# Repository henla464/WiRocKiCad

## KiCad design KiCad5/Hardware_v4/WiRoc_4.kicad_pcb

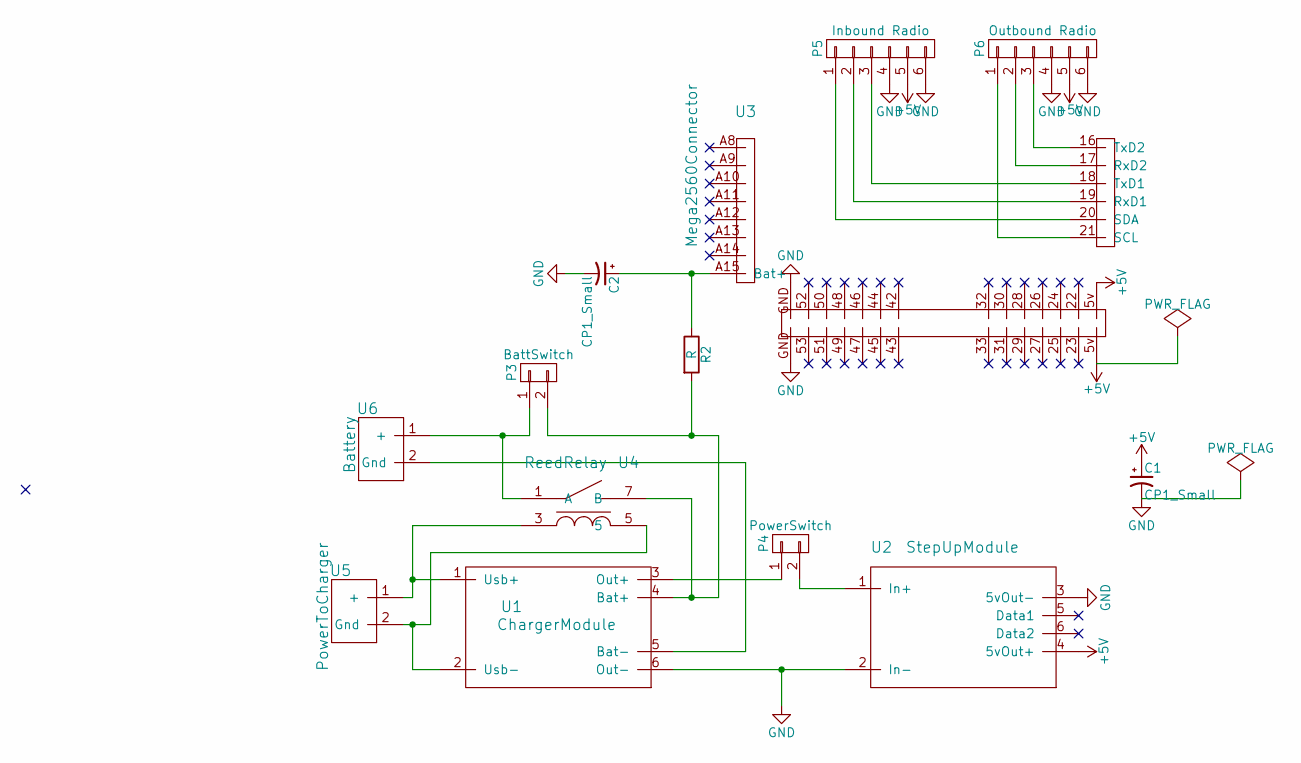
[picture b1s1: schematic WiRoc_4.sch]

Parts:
C1, C2: CP1_Small; C_Radial_D5_L11_P2
P3: BattSwitch; Pin_Header_Straight_1x02
P4: PowerSwitch; Pin_Header_Straight_1x02
P5: Inbound Radio; Pin_Header_Straight_1x06
P6: Outbound Radio; Pin_Header_Straight_1x06
R2: R; Resistor_Horizontal_RM10mm
U1: ChargerModule
U2: StepUpModule
U3: Mega2560Connector
U4: ReedRelay; SIP-1A05
U5: PowerToCharger; JST_2.56
U6: Battery; JST_2.56

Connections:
+5V: C1.1, P5.5, P6.5, U2.4 (5vOut+), U3.5v
GND: C1.2, C2.2, P5.4, P5.6, P6.4, P6.6, U1.6 (Out-), U2.2 (In-), U2.3 (5vOut-), U3.GND
unnamed: C2.1, R2.1, U3.A15 (Bat+)
unnamed: P3.1, U4.1 (A), U6.1 (+)
unnamed: P3.2, R2.2, U1.4 (Bat+), U4.7 (B)
unnamed: P4.1, U1.3 (Out+)
unnamed: P4.2, U2.1 (In+)
unnamed: P5.1, U3.20 (SDA)
unnamed: P5.2, U3.19 (RxD1)
unnamed: P5.3, U3.18 (TxD1)
unnamed: P6.1, U3.21 (SCL)
unnamed: P6.2, U3.17 (RxD2)
unnamed: P6.3, U3.16 (TxD2)
unnamed: U1.1 (Usb+), U4.3, U5.1 (+)
unnamed: U1.2 (Usb-), U4.5, U5.2 (Gnd)
unnamed: U1.5 (Bat-), U6.2 (Gnd)

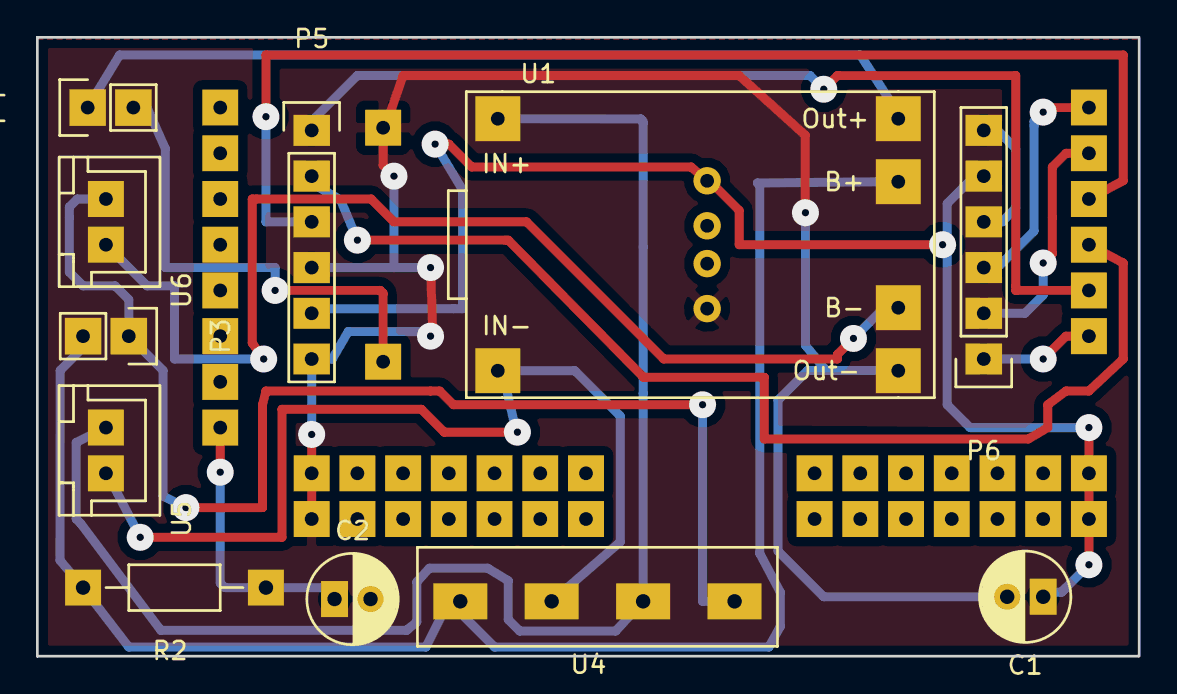
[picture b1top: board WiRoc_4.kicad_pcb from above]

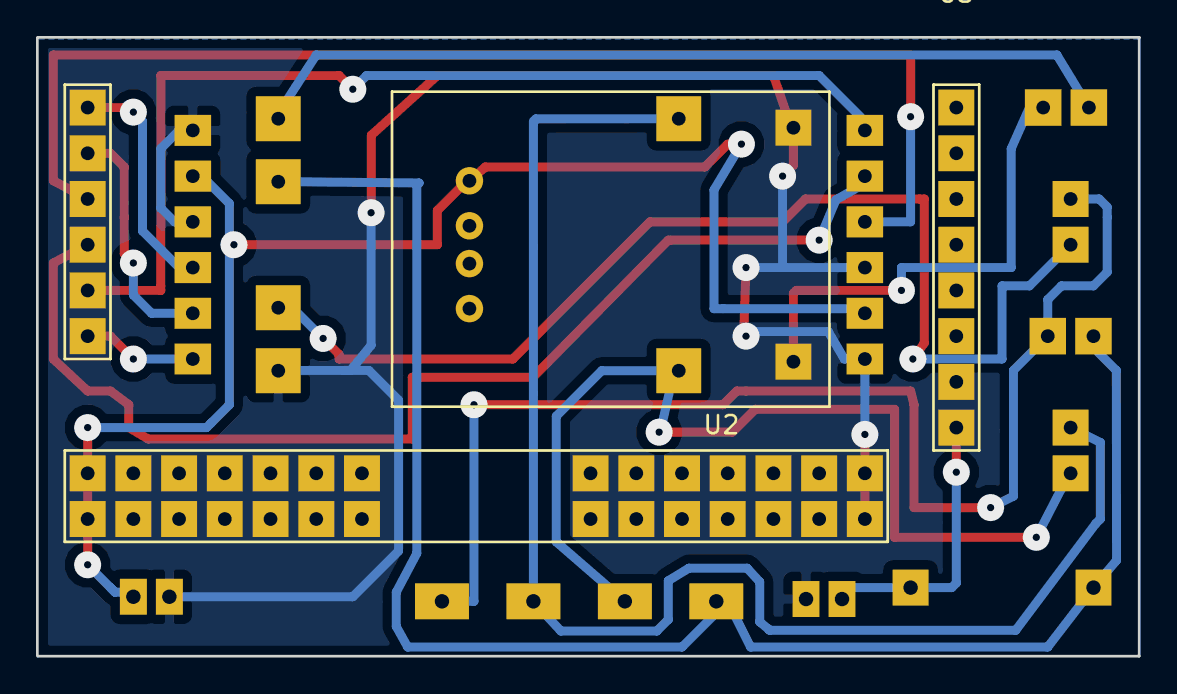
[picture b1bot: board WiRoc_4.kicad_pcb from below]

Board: 2 copper layers, 61.2 x 34.4 mm, 13 parts (2 on the bottom side), 16 nets.

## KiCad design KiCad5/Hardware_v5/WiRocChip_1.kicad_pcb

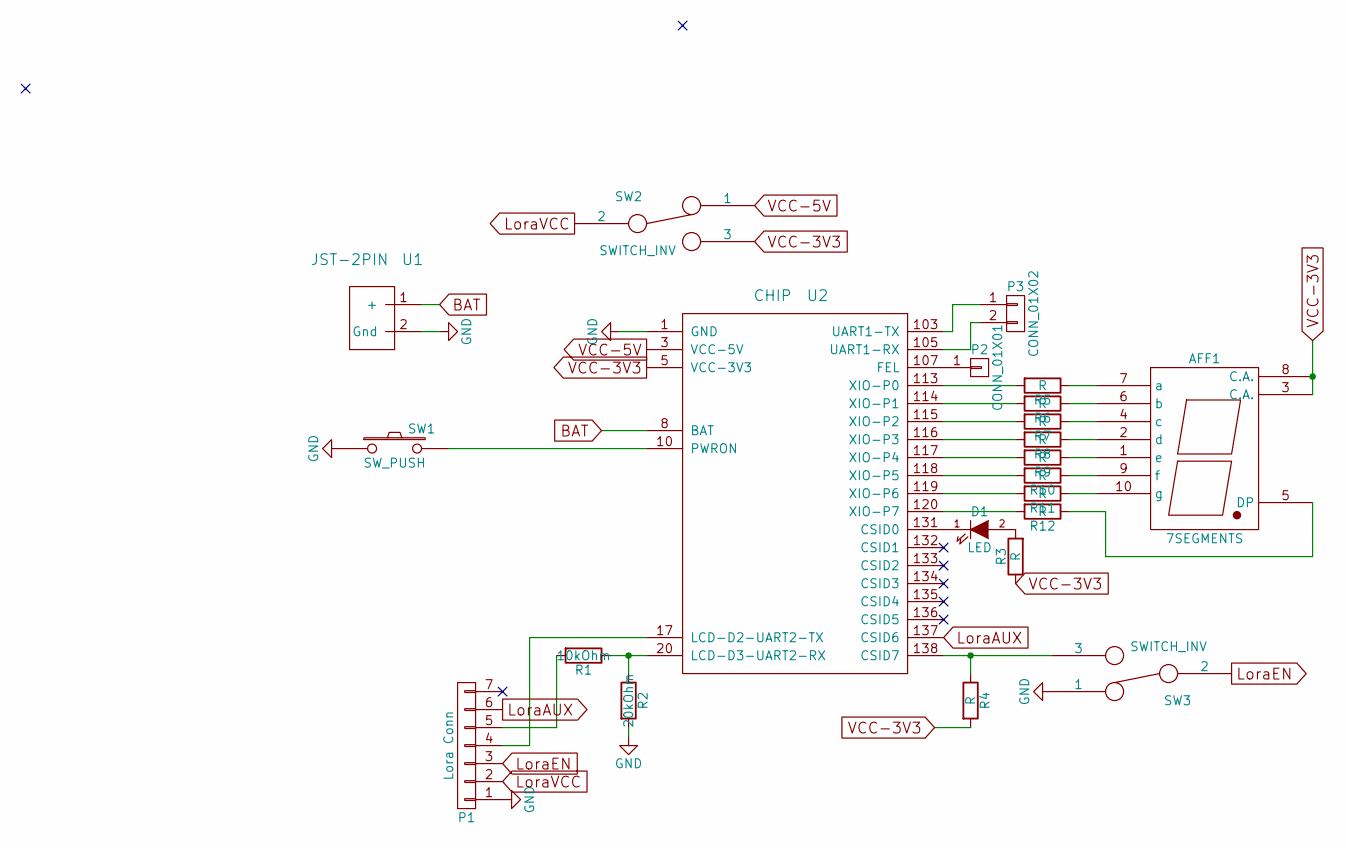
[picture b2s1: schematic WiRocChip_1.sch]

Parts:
AFF1: 7SEGMENTS; 7SegmentLED_LTS6760_LTS6780
D1: LED; LED_D3.0mm
P1: Lora Conn; Pin_Header_Straight_1x07_Pitch2.54mm
P2: CONN_01X01; Pin_Header_Straight_1x01_Pitch2.54mm
P3: CONN_01X02; Pin_Header_Straight_1x02_Pitch2.54mm
R1: 10kOhm; R_Axial_DIN0207_L6.3mm_D2.5mm_P7.62mm_Horizontal
R2: 20kOhm; R_Axial_DIN0207_L6.3mm_D2.5mm_P7.62mm_Horizontal
R3, R4, R5, R6, R7, R8, R9, R10, R11, R12: R; R_Axial_DIN0207_L6.3mm_D2.5mm_P7.62mm_Horizontal
SW1: SW_PUSH; Pin_Header_Straight_1x02_Pitch2.54mm
SW2, SW3: SWITCH_INV; Pin_Header_Straight_1x03_Pitch2.54mm
U1: JST-2PIN; JST_2.56
U2: CHIP; Chip

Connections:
BAT: U1.1 (+), U2.8 (BAT)
GND: P1.1, R2.2, SW1.1, SW3.1, U1.2 (Gnd), U2.1 (GND)
LoraAUX: P1.6, U2.137 (CSID6)
LoraEN: P1.3, SW3.2
LoraVCC: P1.2, SW2.2
unnamed: AFF1.1 (e), R9.1
unnamed: AFF1.2 (d), R8.1
unnamed: AFF1.4 (c), R7.1
unnamed: AFF1.5 (DP), R12.1
unnamed: AFF1.6 (b), R6.1
unnamed: AFF1.7 (a), R5.1
unnamed: AFF1.9 (f), R10.1
unnamed: AFF1.10 (g), R11.1
unnamed: D1.1 (K), U2.131 (CSID0)
unnamed: D1.2 (A), R3.2
unnamed: P1.4, U2.17 (LCD-D2-UART2-TX)
unnamed: P1.5, R1.2
unnamed: P2.1, U2.107 (FEL)
unnamed: P3.1, U2.103 (UART1-TX)
unnamed: P3.2, U2.105 (UART1-RX)
unnamed: R1.1, R2.1, U2.20 (LCD-D3-UART2-RX)
unnamed: R4.1, SW3.3, U2.138 (CSID7)
unnamed: R5.2, U2.113 (XIO-P0)
unnamed: R6.2, U2.114 (XIO-P1)
unnamed: R7.2, U2.115 (XIO-P2)
unnamed: R8.2, U2.116 (XIO-P3)
unnamed: R9.2, U2.117 (XIO-P4)
unnamed: R10.2, U2.118 (XIO-P5)
unnamed: R11.2, U2.119 (XIO-P6)
unnamed: R12.2, U2.120 (XIO-P7)
unnamed: SW1.2, U2.10 (PWRON)
VCC-3V3: AFF1.3 (C.A.), AFF1.8 (C.A.), R3.1, R4.2, SW2.3, U2.5 (VCC-3V3)
VCC-5V: SW2.1, U2.3 (VCC-5V)

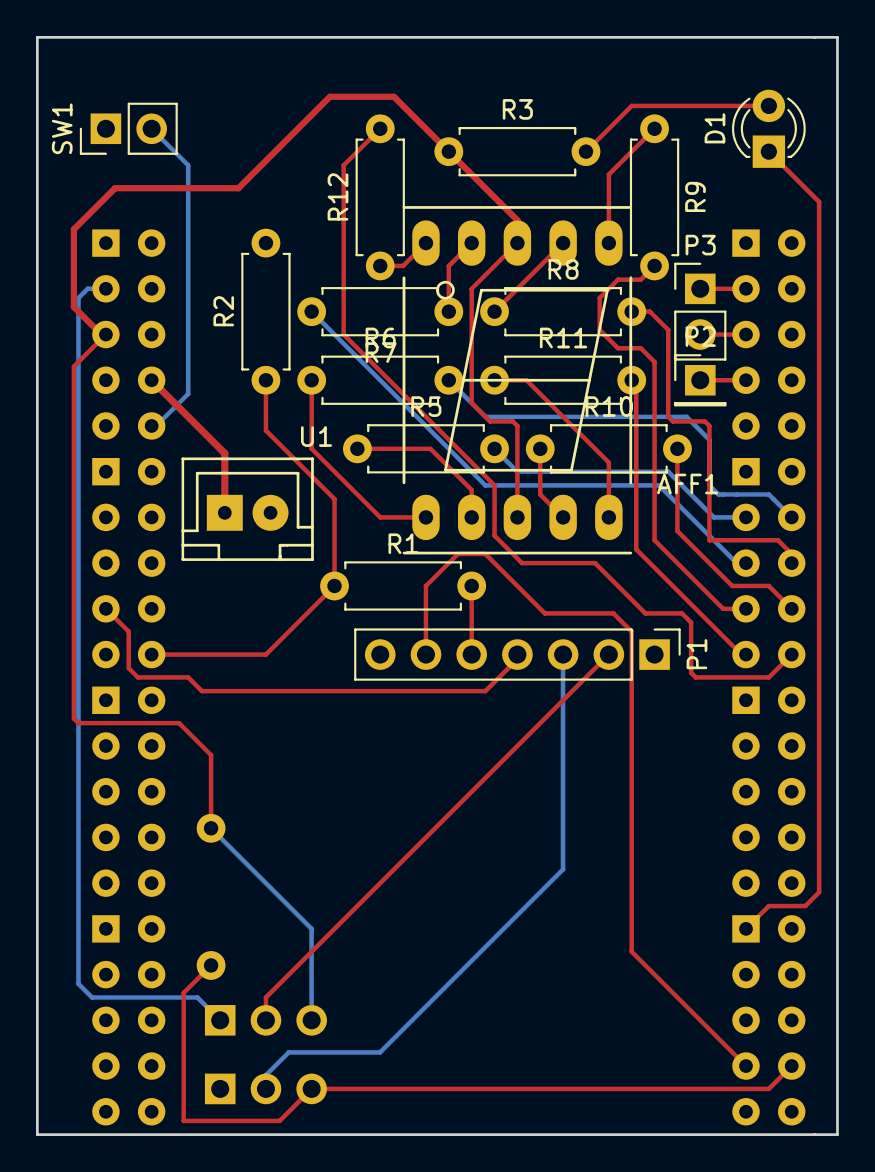
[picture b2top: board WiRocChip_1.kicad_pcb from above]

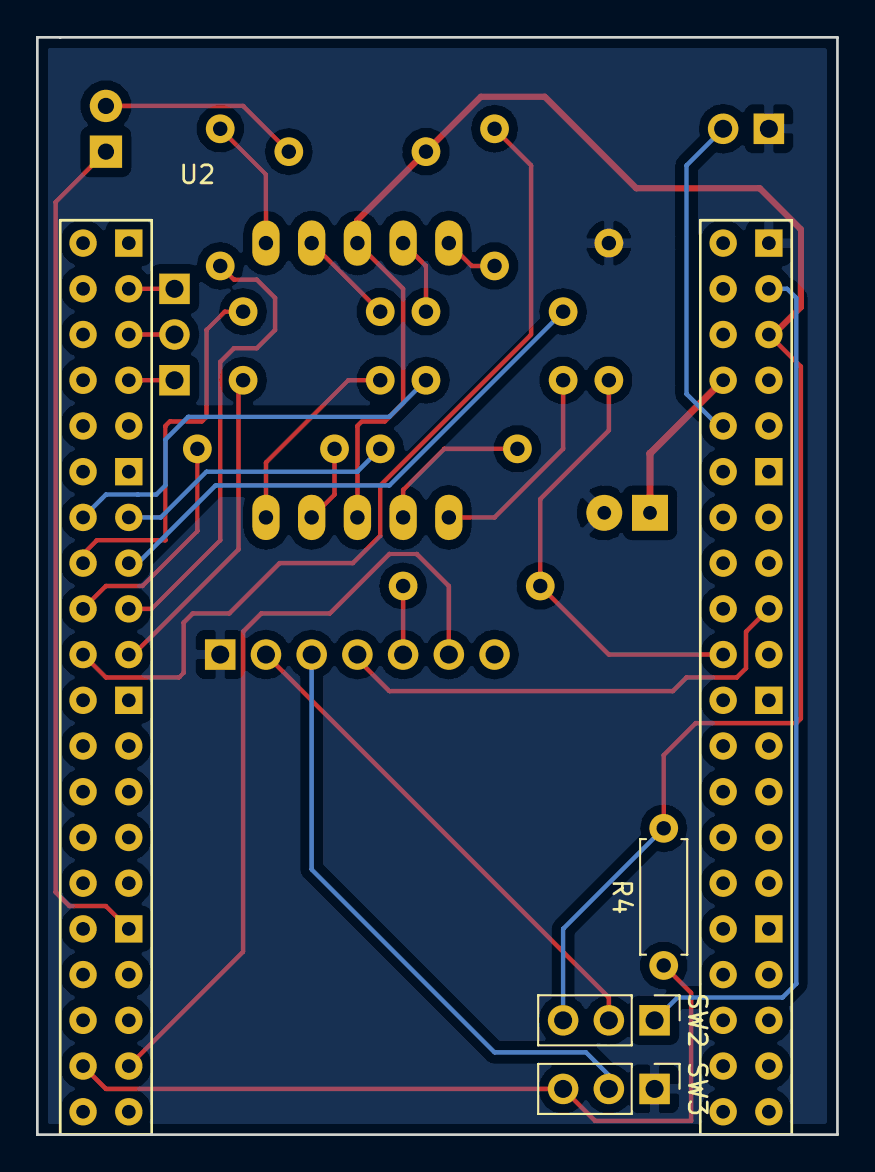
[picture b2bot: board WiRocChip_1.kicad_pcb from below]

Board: 2 copper layers, 44.4 x 61.0 mm, 22 parts (4 on the bottom side), 33 nets.

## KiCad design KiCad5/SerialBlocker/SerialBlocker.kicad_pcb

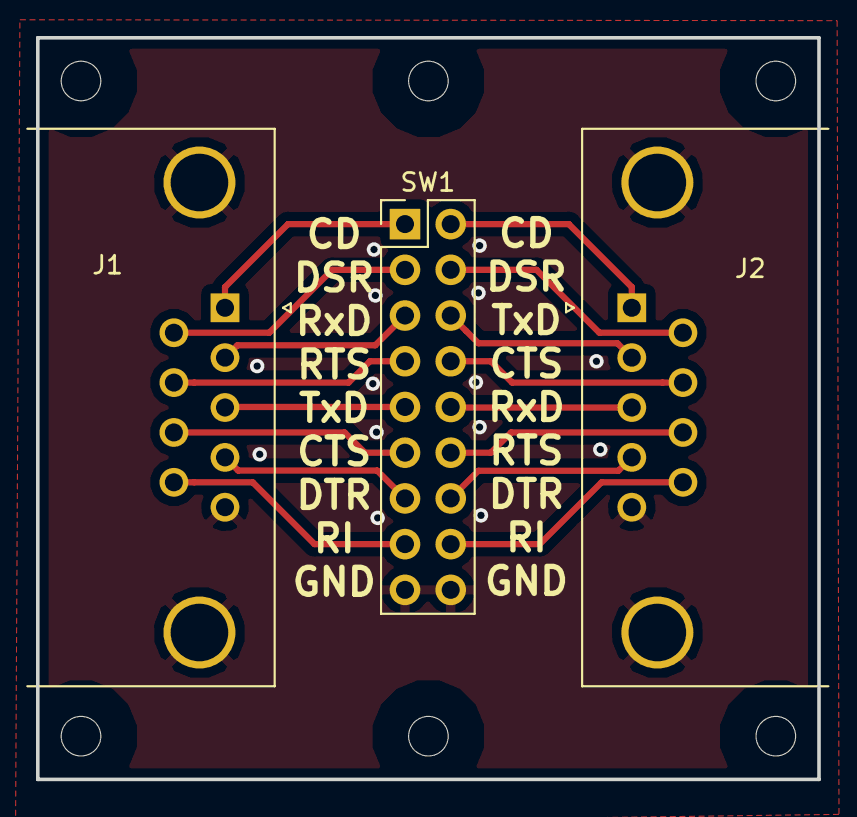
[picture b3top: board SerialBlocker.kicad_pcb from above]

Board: 2 copper layers, 43.4 x 41.2 mm, 3 parts (0 on the bottom side), 17 nets.

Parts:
J1: DB9_Male_MountingHoles; DSUB-9_Male_Horizontal_P2.77x2.84mm_Edge_Housed_MountingHol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
J2: DB9_Female_MountingHoles; DSUB-9_Female_Horizontal_P2.77x2.84mm_Edge_offset6.96mm_cen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
SW1: SW_DIP_x09; PinHeader_Serial_Blocker

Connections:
GND: J1.0, J1.5, J2.0, J2.5, SW1.9, SW1.10
unnamed: J1.1, SW1.1
unnamed: J1.2, SW1.3
unnamed: J1.3, SW1.5
unnamed: J1.4, SW1.7
unnamed: J1.6, SW1.2
unnamed: J1.7, SW1.4
unnamed: J1.8, SW1.6
unnamed: J1.9, SW1.8
unnamed: J2.1, SW1.18
unnamed: J2.2, SW1.16
unnamed: J2.3, SW1.14
unnamed: J2.4, SW1.12
unnamed: J2.6, SW1.17
unnamed: J2.7, SW1.15
unnamed: J2.8, SW1.13
unnamed: J2.9, SW1.11

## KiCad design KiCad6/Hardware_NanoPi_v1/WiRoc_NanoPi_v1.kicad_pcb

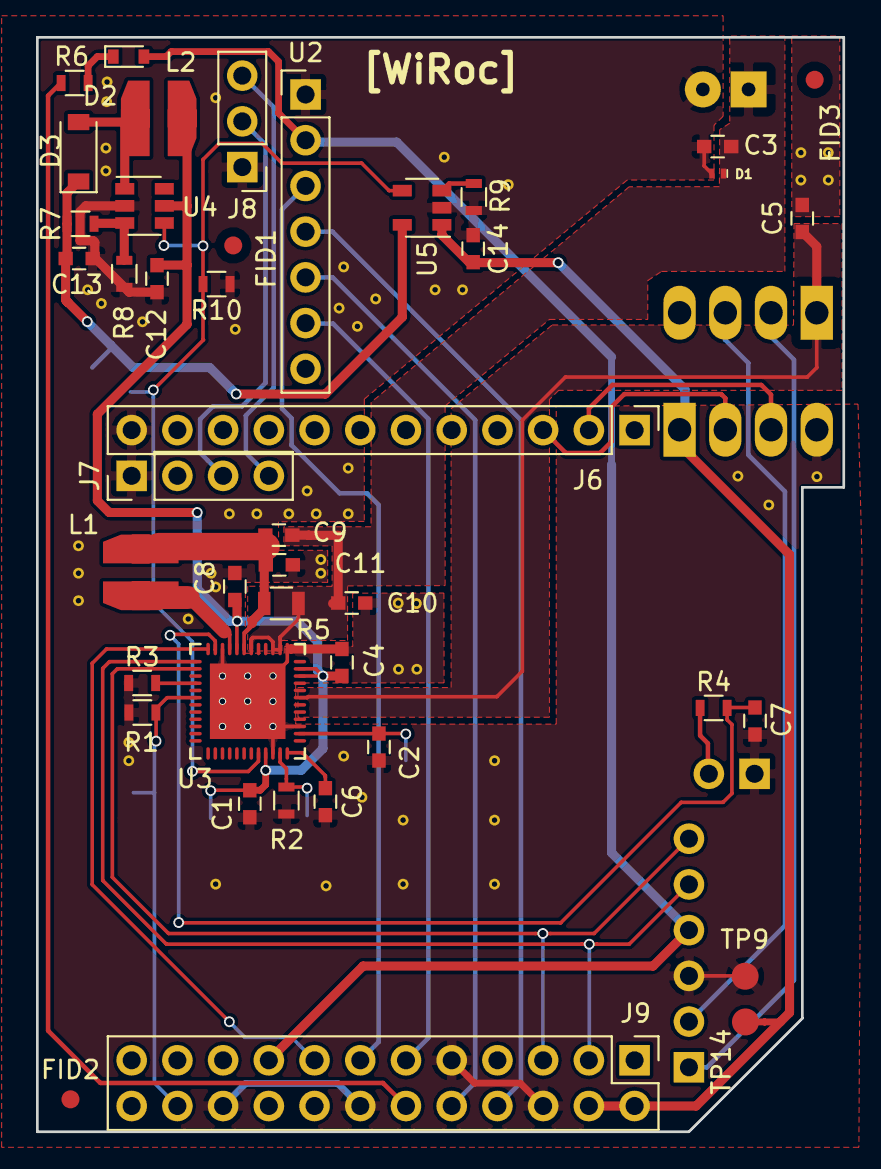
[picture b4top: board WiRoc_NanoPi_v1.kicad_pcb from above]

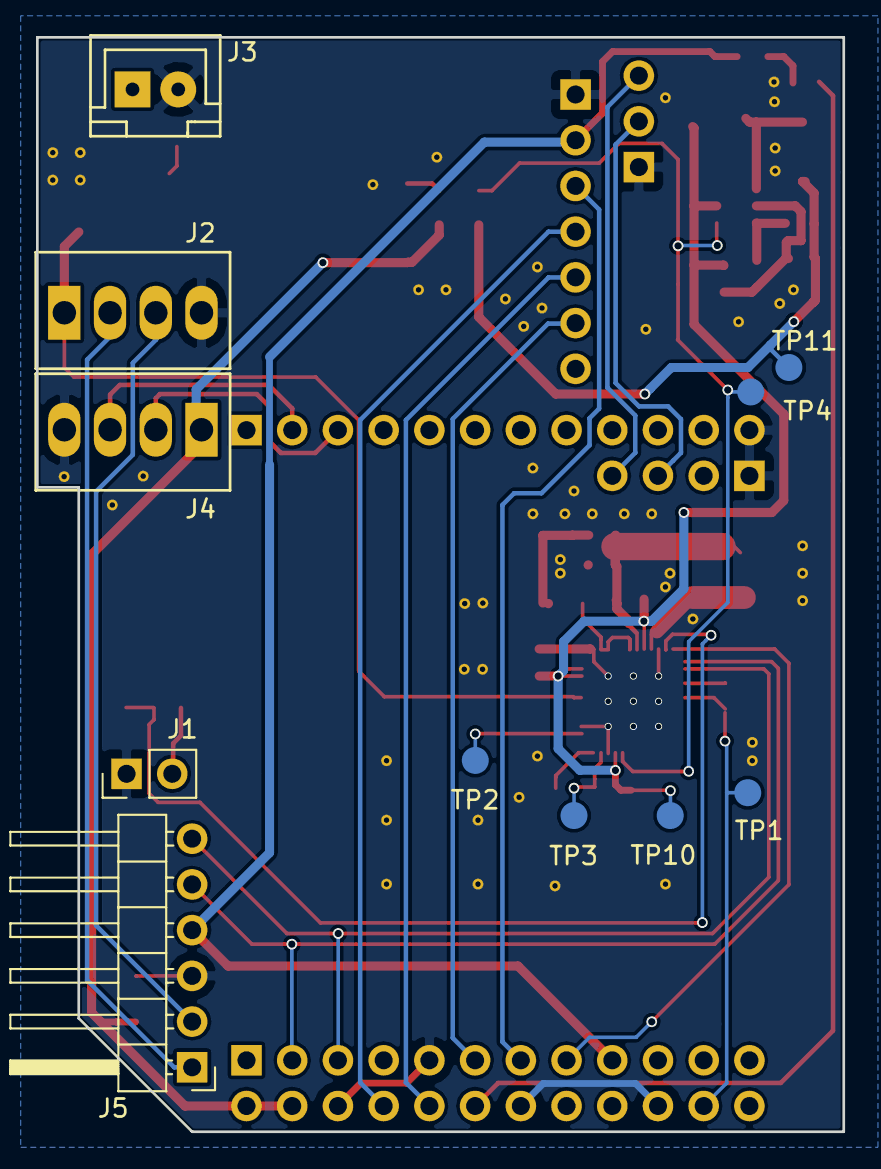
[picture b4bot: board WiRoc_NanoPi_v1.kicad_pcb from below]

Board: 2 copper layers, 44.8 x 60.8 mm, 53 parts (5 on the bottom side), 35 nets.

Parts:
C1, C3, C8, C10, C11: 4.7uF; C_0603
C2, C6, C9: 1uF; C_0603
C4, C5, C12, C13, C14: 10uF; C_0603
C7: 100pF; C_0603
D1: D_TVS; SOD-882L
D2: LED; D_0603
D3: IN5819; D_SOD-123
FID1, FID2, FID3: FIDUCIAL; Fiducial
J1: Conn_01x02; Pin_Header_Straight_1x02_Pitch2.54mm
J2: TerminalBlock_USB_Power_01x04; TerminalBlock_4P_2.54mm
J3: JST-2PIN; JST_2.56
J4: TerminalBlock_USB_Host_Data_01x04; TerminalBlock_4P_2.54mm
J5: Conn_01x06; Pin_Header_Angled_1x06_Pitch2.54mm
J6: NanoPIAir_USBPort; Pin_Header_Straight_1x12_Pitch2.54mm
J7: NanoPIAir_DebugPort; Pin_Header_Straight_1x04_Pitch2.54mm
J8: HAT_Conn_DBG; Pin_Header_Straight_1x03_Pitch2.54mm
J9: NanoPIAir_GPIOPort; Pin_Header_Straight_2x12_Pitch2.54mm
L1, L2: 2.2uH-DCR<0.1R-1.5A; ELL4LG-A
R1, R10: 100K-1%; R_0603
R2, R3, R7: 200K-1%; R_0603
R4, R6: 1K; R_0603
R5: 0R03; R_0805
R8: 24K-1%; R_0603
R9: 3.6K-1%; R_0603
TP1, TP2, TP3, TP4, TP9, TP10, TP11, TP14: TEST; Measurement_Point_Round-SMD-Pad_Small
U2: LoraRadio; Pin_Header_Straight_1x07_Pitch2.54mm
U3: AXP209; qfn48_6x6mm_Pitch0.4mm
U4: LP6226/SY7208; SOT-23-6
U5: SY6280; SOT-23-5

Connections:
BAT: C3.1, C9.1, C10.2, D1.1, J3.1, R5.2, U3.38, U3.39, U3.42
EXTEN: R10.2, TP4.1, U3.20, U4.4, U5.4
GND: C1.2, C2.2, C3.2, C4.2, C5.2, C6.2, C7.1, C8.1, C10.1, C11.1, C12.2, C13.2, C14.2, D1.2, J1.1, J2.4, J3.2, J4.4, J5.3, J6.12, J7.1, J8.1, J9.6, J9.9, J9.14, J9.20, R1.1, R2.1, R3.1, R8.1, R9.1, R10.1, TP9.1, U2.1, U3.22, U3.27, U3.37, U3.46, U3.49, U4.2, U5.2
IPSOUT: C1.1, C4.1, C8.2, C12.1, L2.1, TP10.1, U3.21, U3.34, U3.35, U3.44, U4.5
IRQ: J9.15, U3.48
LORAAUX: J9.11, U2.6
LORAEN: J9.13, U2.3
N_VBUSEN: J9.22, R1.2, TP1.1, U3.6
unnamed: C2.1, TP2.1, U3.26
unnamed: C6.1, U3.24
unnamed: C9.2, C11.2, L1.2, R5.1, U3.43
unnamed: C13.1, D3.1, R7.2, TP11.1, U5.5
unnamed: D2.1, R6.1
unnamed: D3.2, L2.2, U4.1
unnamed: J1.2, R4.1
unnamed: J2.2, J5.1
unnamed: J2.3, J5.2
unnamed: J7.3, J8.2
unnamed: J7.4, J8.3
unnamed: L1.1, U3.45
unnamed: R2.2, TP3.1, U3.23
unnamed: R3.2, U3.4
unnamed: R7.1, R8.2, U4.3
unnamed: R9.2, U5.3
PWRON: C7.2, R4.2, U3.47
SCK: J5.6, J9.5, U3.2
SDA: J5.5, J9.3, U3.1
STATUS_LED: J9.12, R6.2
SYS_3.3V: D2.2, J5.4, J9.17, U2.2
UART1_RX: J9.10, U2.5
UART1_TX: J9.8, U2.4
USBHost-DM1: J4.2, J6.3
USBHost-DP1: J4.3, J6.2
VBUS: C5.1, J2.1, U3.31
VDD_5V: C14.1, J4.1, J9.2, J9.4, TP14.1, U5.1
